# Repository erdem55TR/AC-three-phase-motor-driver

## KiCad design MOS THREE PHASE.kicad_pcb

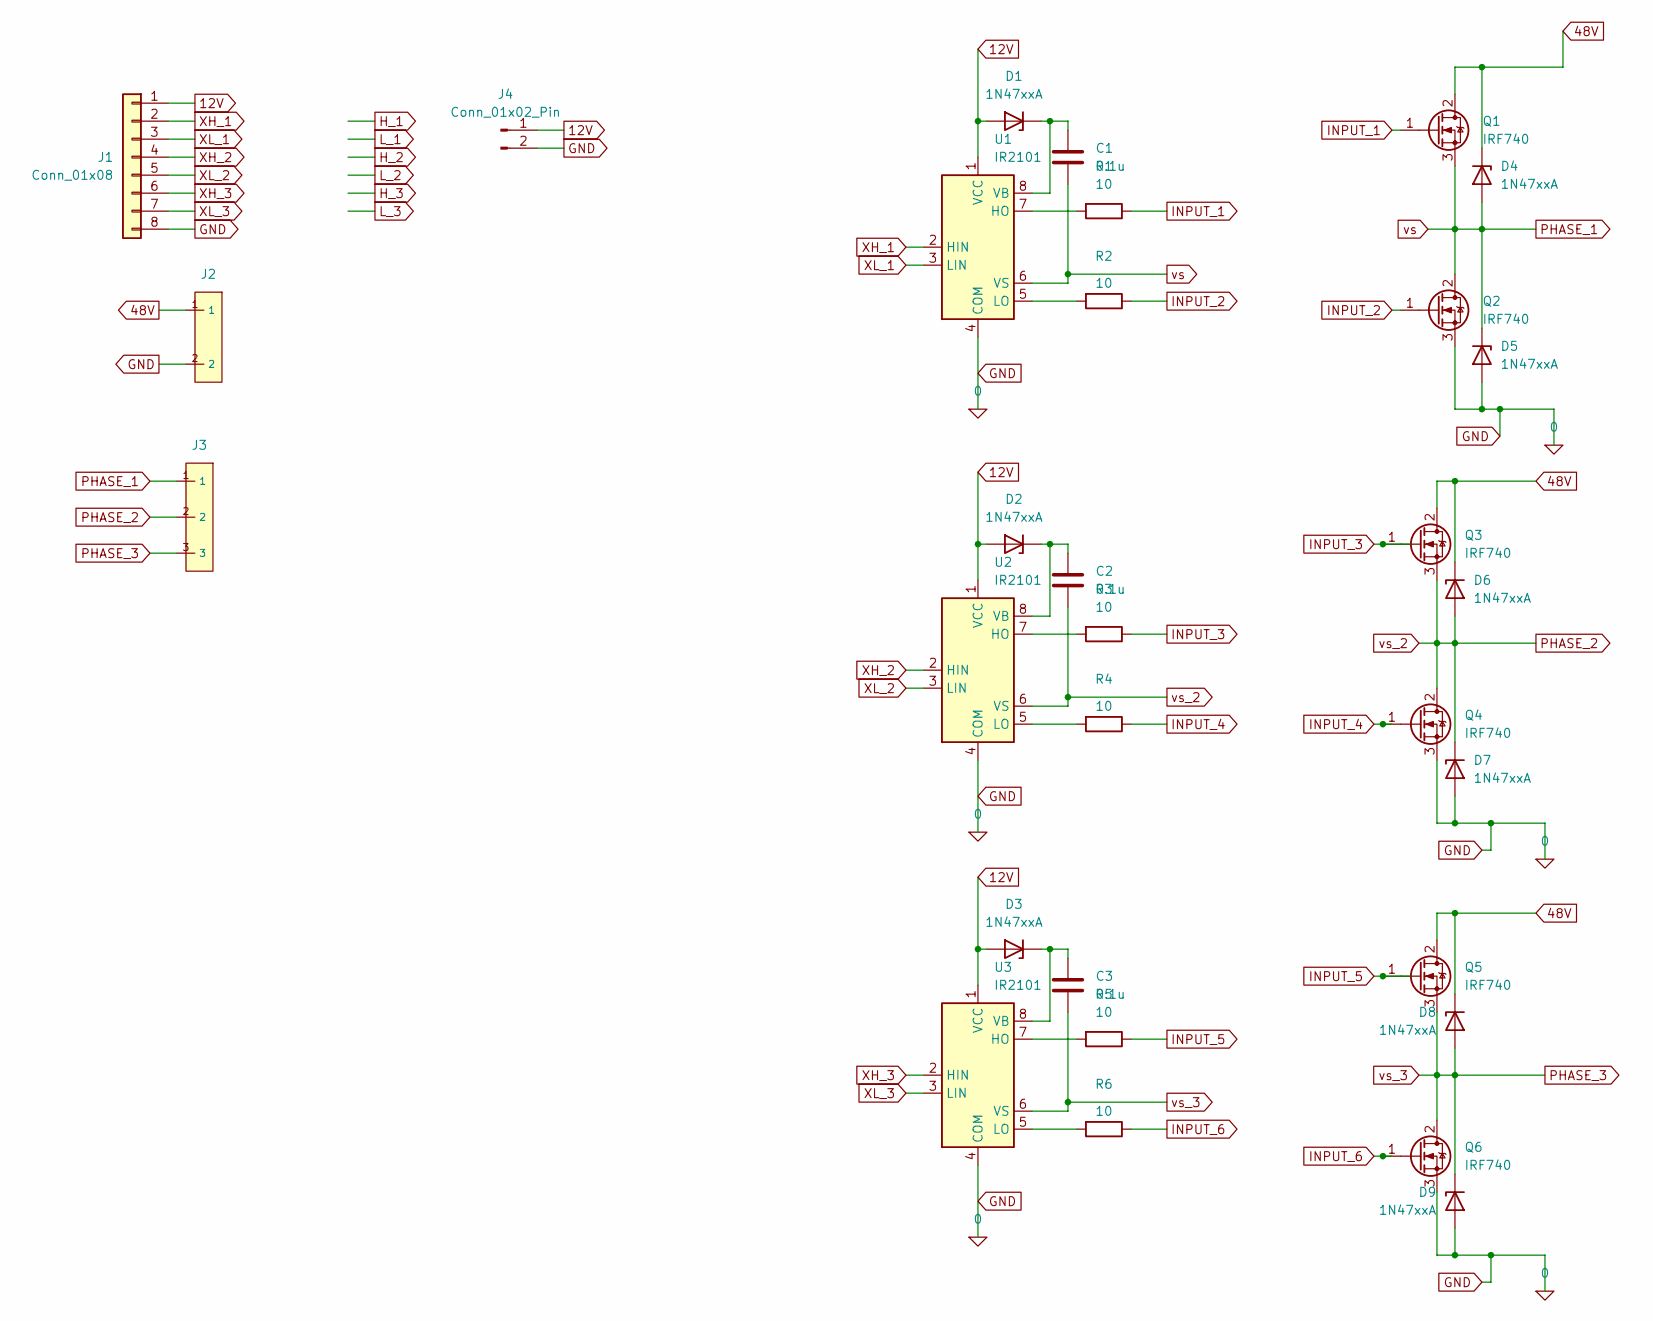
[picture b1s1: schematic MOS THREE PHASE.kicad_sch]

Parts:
C1, C2, C3: 0.1u; CP_Radial_D8.0mm_P5.00mm
D1, D2, D3, D4, D5, D6, D7, D8, D9: 1N47xxA; D_DO-41_SOD81_P10.16mm_Horizontal
J1: Conn_01x08; PinSocket_1x08_P2.54mm_Vertical
J2: PhoenixContact_MCV_1,5_2-G-5.08_1x02_P5.08mm_Vertical
J3: PhoenixContact_MCV_1,5_3-G-5.08_1x03_P5.08mm_Vertical
J4: Conn_01x02_Pin; PhoenixContact_MCV_1,5_2-G-5.08_1x02_P5.08mm_Vertical
Q1, Q2, Q3, Q4, Q5, Q6: IRF740; TO-247-3_Vertical
R1, R2, R3, R4, R5, R6: 10; R_Axial_DIN0207_L6.3mm_D2.5mm_P10.16mm_Horizontal
U1, U2, U3: IR2101; DIP-8_W7.62mm

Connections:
12V: D1.2 (A), D2.2 (A), D3.2 (A), J1.1, J4.1, U1.1 (VCC), U2.1 (VCC), U3.1 (VCC)
48V: D4.1 (K), D6.1 (K), D8.1 (K), J2.1, Q1.2 (D), Q3.2 (D), Q5.2 (D)
GND: D5.2 (A), D7.2 (A), D9.2 (A), J1.8, J2.2, J4.2, Q2.3 (S), Q4.3 (S), Q6.3 (S), U1.4 (COM), U2.4 (COM), U3.4 (COM)
INPUT_1: Q1.1 (G), R1.1
INPUT_2: Q2.1 (G), R2.1
INPUT_3: Q3.1 (G), R3.1
INPUT_4: Q4.1 (G), R4.1
INPUT_5: Q5.1 (G), R5.1
INPUT_6: Q6.1 (G), R6.1
unnamed: C1.1, D1.1 (K), U1.8 (VB)
unnamed: C2.1, D2.1 (K), U2.8 (VB)
unnamed: C3.1, D3.1 (K), U3.8 (VB)
unnamed: R1.2, U1.7 (HO)
unnamed: R2.2, U1.5 (LO)
unnamed: R3.2, U2.7 (HO)
unnamed: R4.2, U2.5 (LO)
unnamed: R5.2, U3.7 (HO)
unnamed: R6.2, U3.5 (LO)
PHASE_1: C1.2, D4.2 (A), D5.1 (K), J3.1, Q1.3 (S), Q2.2 (D), U1.6 (VS)
PHASE_2: C2.2, D6.2 (A), D7.1 (K), J3.2, Q3.3 (S), Q4.2 (D), U2.6 (VS)
PHASE_3: C3.2, D8.2 (A), D9.1 (K), J3.3, Q5.3 (S), Q6.2 (D), U3.6 (VS)
XH_1: J1.2, U1.2 (HIN)
XH_2: J1.4, U2.2 (HIN)
XH_3: J1.6, U3.2 (HIN)
XL_1: J1.3, U1.3 (LIN)
XL_2: J1.5, U2.3 (LIN)
XL_3: J1.7, U3.3 (LIN)

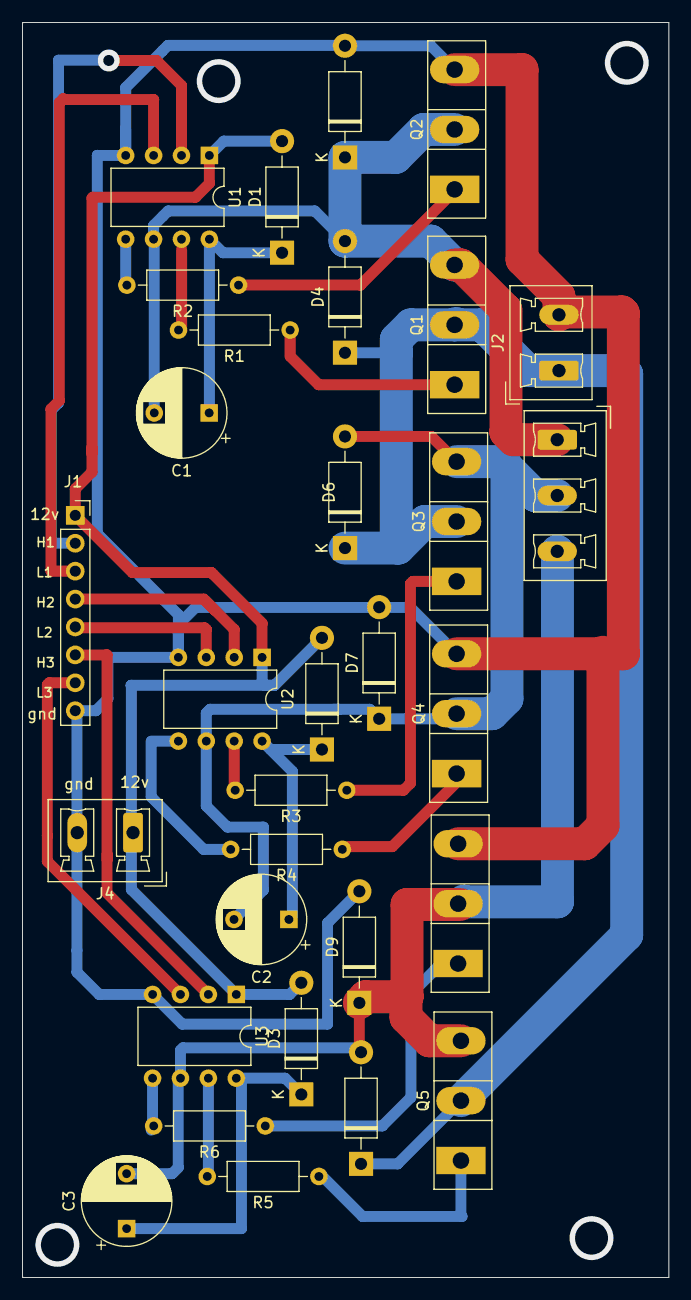
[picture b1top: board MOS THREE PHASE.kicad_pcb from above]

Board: 2 copper layers, 58.8 x 114.2 mm, 31 parts (0 on the bottom side), 27 nets.
